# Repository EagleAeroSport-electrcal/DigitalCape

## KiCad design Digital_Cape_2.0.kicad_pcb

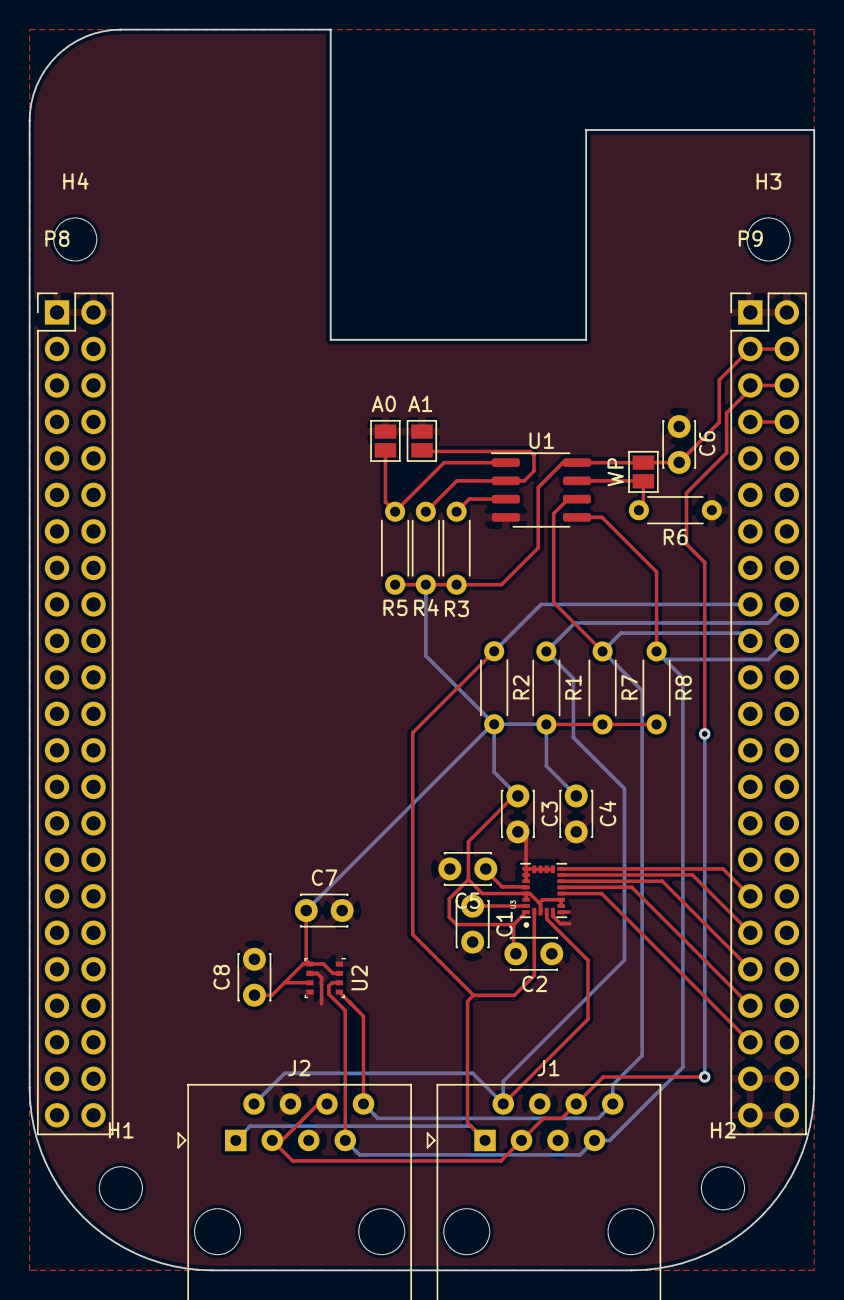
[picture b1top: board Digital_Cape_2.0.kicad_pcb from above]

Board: 2 copper layers, 54.6 x 86.4 mm, 30 parts (0 on the bottom side), 19 nets.

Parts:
C1, C2, C3, C7, C8: 100nF; C_Disc_D3.0mm_W2.0mm_P2.50mm
C4: 10uF; C_Disc_D3.0mm_W2.0mm_P2.50mm
C5: 10nF; C_Disc_D3.0mm_W2.0mm_P2.50mm
C6: 0.1u; C_Disc_D3.0mm_W2.0mm_P2.50mm
H1, H2, H3, H4: MountingHole; MountingHole_3mm
J1, J2: RJ45; RJ45_Amphenol_54602-x08_Horizontal
JP1: A0; SolderJumper-2_P1.3mm_Open_Pad1.0x1.5mm
JP2: A1; SolderJumper-2_P1.3mm_Open_Pad1.0x1.5mm
JP3: WP; SolderJumper-2_P1.3mm_Open_Pad1.0x1.5mm
P8, P9: BeagleBone_Black_Header; PinHeader_2x23_P2.54mm_Vertical
R1, R2, R3, R4, R5, R7, R8: 4.7k; R_Axial_DIN0204_L3.6mm_D1.6mm_P5.08mm_Horizontal
R6: 10k; R_Axial_DIN0204_L3.6mm_D1.6mm_P5.08mm_Horizontal
U1: CAT24C256; SOIC-8_3.9x4.9mm_P1.27mm
U2: BME_280; Bosch_LGA-8_2.5x2.5mm_P0.65mm_ClockwisePinNumbering
U3: LSM9_DS1

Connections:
+3V3: C2.1, C3.1, C4.1, C6.1, C7.1, C8.1, JP3.1, P9.3, P9.4, R1.2, R2.2, R3.1, R4.1, R5.1, R7.2, R8.2, U1.8, U2.2, U2.6, U2.8, U3.1, U3.3, U3.7, U3.8, U3.22, U3.23
+5V: J1.3, J1.6, J2.3, J2.6, P9.5, P9.6
/DRDY_M: P9.39, U3.10
/I2C1_SCL: J1.1, J2.1, P9.17, R2.1, U3.2
/I2C1_SDA: J1.2, J2.2, P9.18, R1.1, U3.4
/I2C2_SCL: J1.8, J2.8, P9.19, R7.1, U1.6, U2.4
/I2C2_SDA: J1.7, J2.7, P9.20, R8.1, U1.5, U2.3
/INT1_A: P9.37, U3.11
/INT2_A: P9.35, U3.12
/INT_M: P9.41, U3.9
/LSM9_EN: P9.33, U3.13
GND: C1.2, C2.2, C3.2, C4.2, C5.2, C6.2, C7.2, C8.2, J1.4, J1.5, J2.4, J2.5, JP1.2, JP2.2, P8.1, P8.2, P9.1, P9.2, P9.43, P9.44, P9.45, P9.46, R6.2, U1.4, U2.1, U2.5, U2.7, U3.5, U3.6, U3.14, U3.15, U3.16, U3.17, U3.18, U3.19, U3.20
unnamed: C1.1, U3.24
unnamed: C5.1, U3.21
unnamed: JP1.1, R5.2, U1.1
unnamed: JP2.1, R4.2, U1.2
unnamed: JP3.2, R6.1, U1.7
unnamed: R3.2, U1.3
SYS_5V: P9.7, P9.8

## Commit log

2021-02-03 Add gitignore and remove ignored files.
2021-02-14 Update of KiCad files
    My apologies I'm still learning! Files from 02-13-2021 Hangar session
2021-02-15 Update board to fit BBB cape spec
2021-02-15 Switch BME to use standard library component
2021-02-15 Fix LSM9DS1
2021-02-15 Switch pin headers to default libs
2021-02-15 Remove unused libs
2021-02-15 Add power flags
2021-02-15 Add copper pour
2021-02-15 Reposition RJ12 ports
